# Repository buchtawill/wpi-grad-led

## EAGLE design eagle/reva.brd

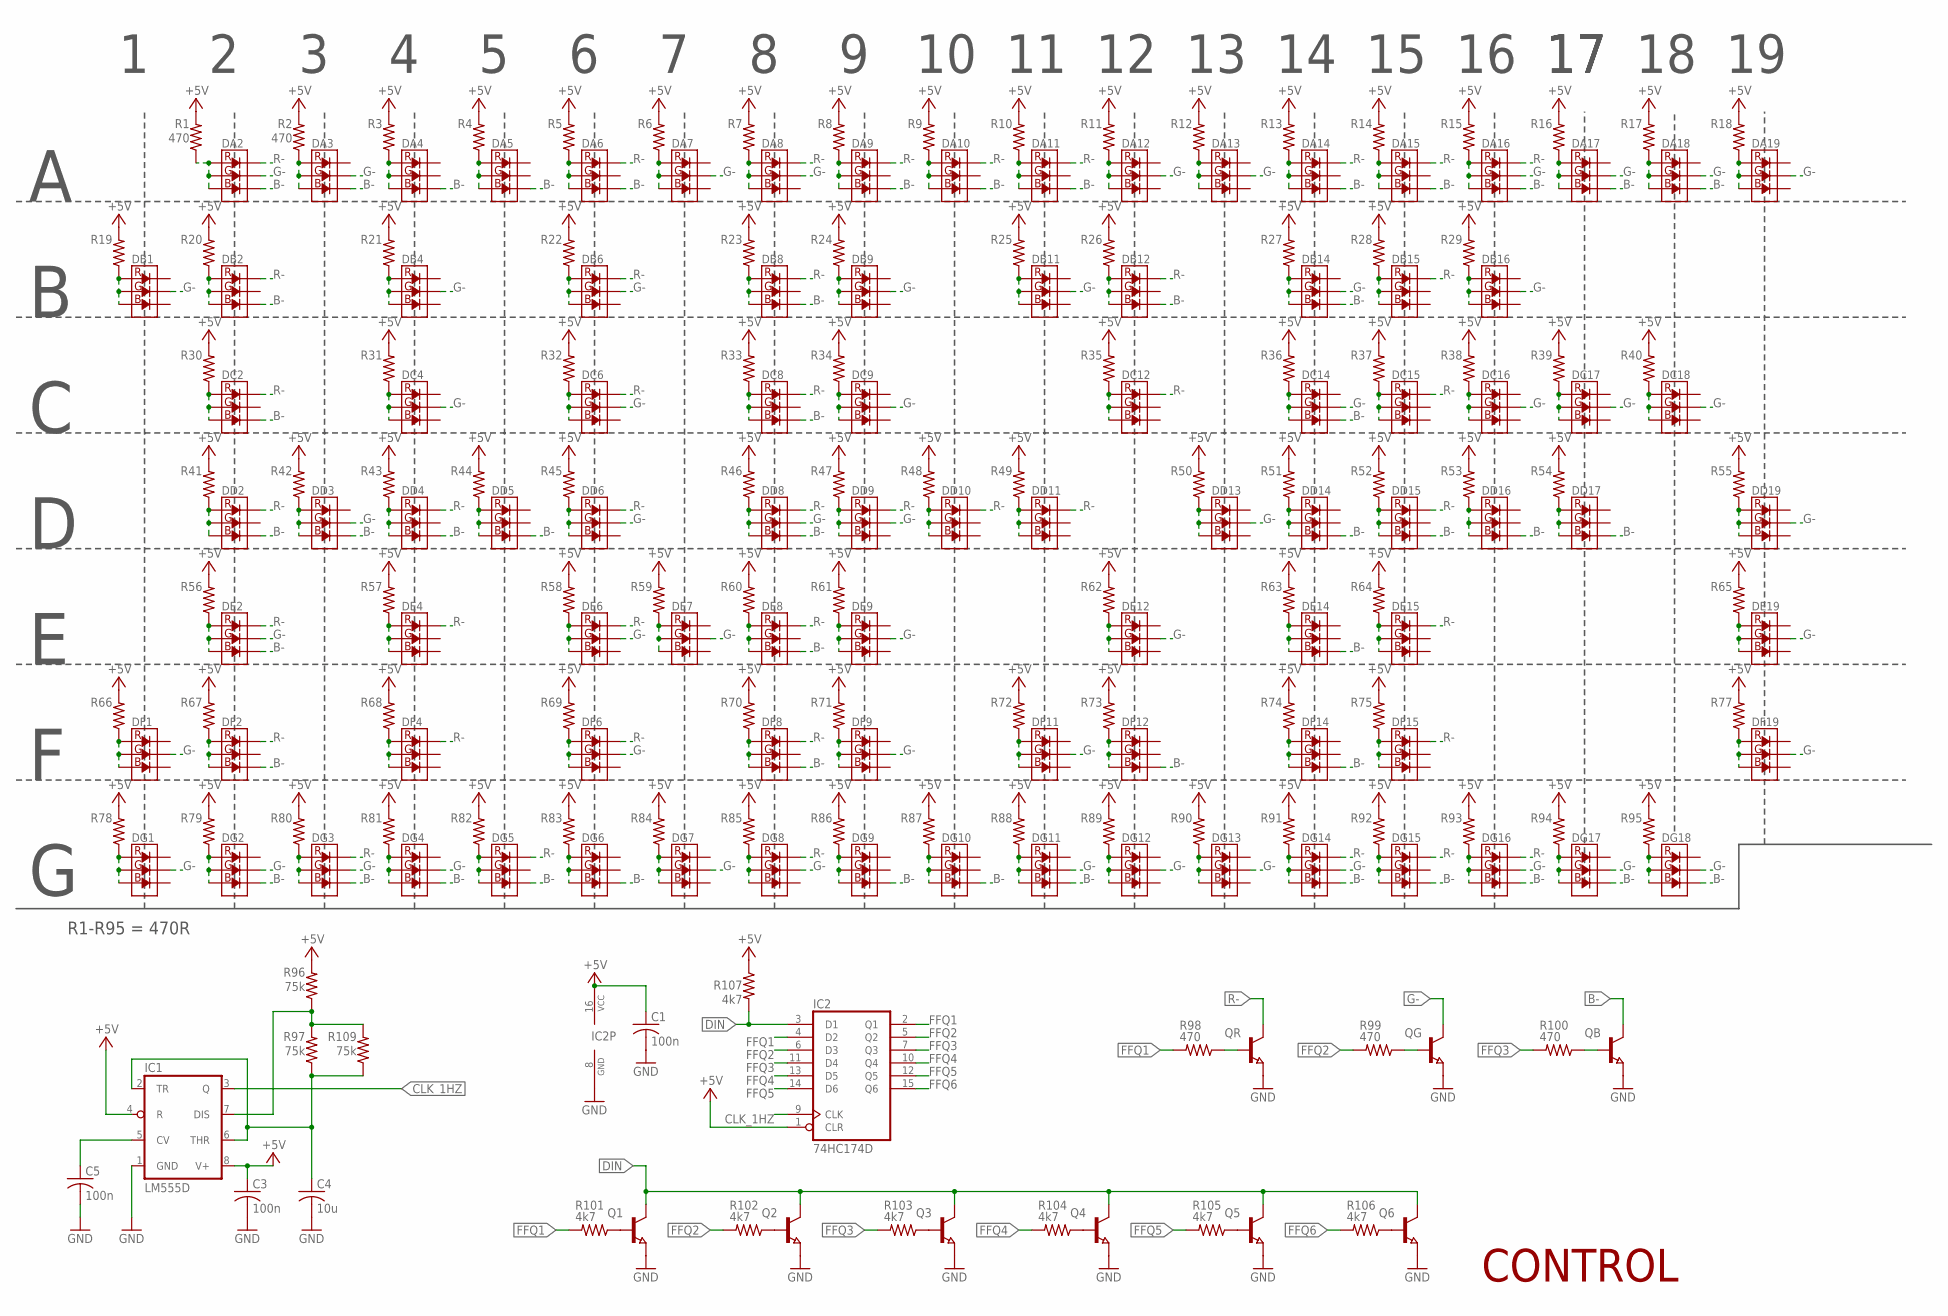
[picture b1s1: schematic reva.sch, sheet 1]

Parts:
C1, C3, C5: 100n; C0603
C4: 10u; C0805
DA2, DA3, DA4, DA5, DA6, DA7, DA8, DA9, DA10, DA11, DA12, DA13, DA14, DA15, DA16, DA17, DA18, DA19: RGB_LED_XL; LED2727
DB1, DB2, DB4, DB6, DB8, DB9, DB11, DB12, DB14, DB15, DB16: RGB_LED_XL; LED2727
DC2, DC4, DC6, DC8, DC9, DC12, DC14, DC15, DC16, DC17, DC18: RGB_LED_XL; LED2727
DD2, DD3, DD4, DD5, DD6, DD8, DD9, DD10, DD11, DD13, DD14, DD15, DD16, DD17, DD19: RGB_LED_XL; LED2727
DE2, DE4, DE6, DE7, DE8, DE9, DE12, DE14, DE15, DE19: RGB_LED_XL; LED2727
DF1, DF2, DF4, DF6, DF8, DF9, DF11, DF12, DF14, DF15, DF19: RGB_LED_XL; LED2727
DG1, DG2, DG3, DG4, DG5, DG6, DG7, DG8, DG9, DG10, DG11, DG12, DG13, DG14, DG15, DG16, DG17, DG18: RGB_LED_XL; LED2727
IC1: LM555D; SO08
IC2: 74HC174D; SO16
Q1, Q2, Q3, Q4, Q5, Q6: NPN-TRANSISTOR_SOT23; SOT23
QB: NPN-TRANSISTOR_SOT23; SOT23
QG: NPN-TRANSISTOR_SOT23; SOT23
QR: NPN-TRANSISTOR_SOT23; SOT23
R1, R2, R98, R99, R100: 470; R0603
R3, R4, R5, R6, R7, R8, R9, R10, R11, R12, R13, R14, R15, R16, R17, R18, R19, R20, R21, R22, R23, R24, R25, R26, R27, R28, R29, R30, R31, R32, R33, R34, R35, R36, R37, R38, R39, R40, R41, R42, R43, R44, R45, R46, R47, R48, R49, R50, R51, R52, R53, R54, R55, R56, R57, R58, R59, R60, R61, R62, R63, R64, R65, R66, R67, R68, R69, R70, R71, R72, R73, R74, R75, R77, R78, R79, R80, R81, R82, R83, R84, R85, R86, R87, R88, R89, R90, R91, R92, R93, R94, R95: R-US_R0603; R0603
R96, R97, R109: 75k; R0603
R101, R102, R103, R104, R105, R106, R107: 4k7; R0603

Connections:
+5V: C1.1, C3.1, IC1.4 (R), IC1.8 (V+), IC2.1 (CLR), IC2.16 (VCC), R1.2, R2.2, R3.2, R4.2, R5.2, R6.2, R7.2, R8.2, R9.2, R10.2, R11.2, R12.2, R13.2, R14.2, R15.2, R16.2, R17.2, R18.2, R19.2, R20.2, R21.2, R22.2, R23.2, R24.2, R25.2, R26.2, R27.2, R28.2, R29.2, R30.2, R31.2, R32.2, R33.2, R34.2, R35.2, R36.2, R37.2, R38.2, R39.2, R40.2, R41.2, R42.2, R43.2, R44.2, R45.2, R46.2, R47.2, R48.2, R49.2, R50.2, R51.2, R52.2, R53.2, R54.2, R55.2, R56.2, R57.2, R58.2, R59.2, R60.2, R61.2, R62.2, R63.2, R64.2, R65.2, R66.2, R67.2, R68.2, R69.2, R70.2, R71.2, R72.2, R73.2, R74.2, R75.2, R77.2, R78.2, R79.2, R80.2, R81.2, R82.2, R83.2, R84.2, R85.2, R86.2, R87.2, R88.2, R89.2, R90.2, R91.2, R92.2, R93.2, R94.2, R95.2, R96.2, R107.1; also elsewhere on the board
B-: DA2.1 (B-), DA3.1 (B-), DA4.1 (B-), DA5.1 (B-), DA6.1 (B-), DA9.1 (B-), DA10.1 (B-), DA11.1 (B-), DA14.1 (B-), DA15.1 (B-), DA16.1 (B-), DA17.1 (B-), DA18.1 (B-), DB2.1 (B-), DB8.1 (B-), DB12.1 (B-), DB14.1 (B-), DC2.1 (B-), DC8.1 (B-), DC14.1 (B-), DD2.1 (B-), DD3.1 (B-), DD4.1 (B-), DD5.1 (B-), DD8.1 (B-), DD14.1 (B-), DD15.1 (B-), DD16.1 (B-), DD17.1 (B-), DE2.1 (B-), DE8.1 (B-), DE14.1 (B-), DF2.1 (B-), DF8.1 (B-), DF12.1 (B-), DF14.1 (B-), DG2.1 (B-), DG3.1 (B-), DG4.1 (B-), DG5.1 (B-), DG6.1 (B-), DG9.1 (B-), DG10.1 (B-), DG11.1 (B-), DG14.1 (B-), DG15.1 (B-), DG16.1 (B-), DG17.1 (B-), DG18.1 (B-), QB.3 (C)
CLK_1HZ: IC1.3 (Q), IC2.9 (CLK)
CV: C5.1, IC1.5 (CV)
DIN: IC2.3 (D1), Q1.3 (C), Q2.3 (C), Q3.3 (C), Q4.3 (C), Q5.3 (C), Q6.3 (C), R107.2
DIS: IC1.7 (DIS), R96.1, R97.2, R109.2
FFQ1: IC2.2 (Q1), IC2.4 (D2), R98.2, R101.2
FFQ2: IC2.5 (Q2), IC2.6 (D3), R99.2, R102.2
FFQ3: IC2.7 (Q3), IC2.11 (D4), R100.2, R103.2
FFQ4: IC2.10 (Q4), IC2.13 (D5), R104.2
FFQ5: IC2.12 (Q5), IC2.14 (D6), R105.2
FFQ6: IC2.15 (Q6), R106.2
G-: DA2.2 (G-), DA3.2 (G-), DA7.2 (G-), DA8.2 (G-), DA12.2 (G-), DA13.2 (G-), DA16.2 (G-), DA17.2 (G-), DA18.2 (G-), DA19.2 (G-), DB1.2 (G-), DB4.2 (G-), DB6.2 (G-), DB9.2 (G-), DB11.2 (G-), DB14.2 (G-), DB16.2 (G-), DC4.2 (G-), DC6.2 (G-), DC9.2 (G-), DC14.2 (G-), DC16.2 (G-), DC17.2 (G-), DC18.2 (G-), DD3.2 (G-), DD6.2 (G-), DD8.2 (G-), DD9.2 (G-), DD13.2 (G-), DD19.2 (G-), DE2.2 (G-), DE6.2 (G-), DE7.2 (G-), DE9.2 (G-), DE12.2 (G-), DE19.2 (G-), DF1.2 (G-), DF6.2 (G-), DF9.2 (G-), DF11.2 (G-), DF19.2 (G-), DG1.2 (G-), DG2.2 (G-), DG3.2 (G-), DG4.2 (G-), DG7.2 (G-), DG8.2 (G-), DG11.2 (G-), DG12.2 (G-), DG13.2 (G-), DG14.2 (G-), DG16.2 (G-), DG17.2 (G-), DG18.2 (G-), QG.3 (C)
GND: C1.2, C3.2, C4.2, C5.2, IC1.1 (GND), IC2.8 (GND), Q1.2 (E), Q2.2 (E), Q3.2 (E), Q4.2 (E), Q5.2 (E), Q6.2 (E), QB.2 (E), QG.2 (E), QR.2 (E); also elsewhere on the board
unnamed: DA2.4 (R+), DA2.5 (G+), DA2.6 (B+), R1.1
unnamed: DA3.4 (R+), DA3.5 (G+), DA3.6 (B+), R2.1
unnamed: DA4.4 (R+), DA4.5 (G+), DA4.6 (B+), R3.1
unnamed: DA5.4 (R+), DA5.5 (G+), DA5.6 (B+), R4.1
unnamed: DA6.4 (R+), DA6.5 (G+), DA6.6 (B+), R5.1
unnamed: DA7.4 (R+), DA7.5 (G+), DA7.6 (B+), R6.1
unnamed: DA8.4 (R+), DA8.5 (G+), DA8.6 (B+), R7.1
unnamed: DA9.4 (R+), DA9.5 (G+), DA9.6 (B+), R8.1
unnamed: DA10.4 (R+), DA10.5 (G+), DA10.6 (B+), R9.1
unnamed: DA11.4 (R+), DA11.5 (G+), DA11.6 (B+), R10.1
unnamed: DA12.4 (R+), DA12.5 (G+), DA12.6 (B+), R11.1
unnamed: DA13.4 (R+), DA13.5 (G+), DA13.6 (B+), R12.1
unnamed: DA14.4 (R+), DA14.5 (G+), DA14.6 (B+), R13.1
unnamed: DA15.4 (R+), DA15.5 (G+), DA15.6 (B+), R14.1
unnamed: DA16.4 (R+), DA16.5 (G+), DA16.6 (B+), R15.1
unnamed: DA17.4 (R+), DA17.5 (G+), DA17.6 (B+), R16.1
unnamed: DA18.4 (R+), DA18.5 (G+), DA18.6 (B+), R17.1
unnamed: DA19.4 (R+), DA19.5 (G+), DA19.6 (B+), R18.1
unnamed: DB1.4 (R+), DB1.5 (G+), DB1.6 (B+), R19.1
unnamed: DB2.4 (R+), DB2.5 (G+), DB2.6 (B+), R20.1
unnamed: DB4.4 (R+), DB4.5 (G+), DB4.6 (B+), R21.1
unnamed: DB6.4 (R+), DB6.5 (G+), DB6.6 (B+), R22.1
unnamed: DB8.4 (R+), DB8.5 (G+), DB8.6 (B+), R23.1
unnamed: DB9.4 (R+), DB9.5 (G+), DB9.6 (B+), R24.1
unnamed: DB11.4 (R+), DB11.5 (G+), DB11.6 (B+), R25.1
unnamed: DB12.4 (R+), DB12.5 (G+), DB12.6 (B+), R26.1
unnamed: DB14.4 (R+), DB14.5 (G+), DB14.6 (B+), R27.1
unnamed: DB15.4 (R+), DB15.5 (G+), DB15.6 (B+), R28.1
unnamed: DB16.4 (R+), DB16.5 (G+), DB16.6 (B+), R29.1
unnamed: DC2.4 (R+), DC2.5 (G+), DC2.6 (B+), R30.1
unnamed: DC4.4 (R+), DC4.5 (G+), DC4.6 (B+), R31.1
unnamed: DC6.4 (R+), DC6.5 (G+), DC6.6 (B+), R32.1
unnamed: DC8.4 (R+), DC8.5 (G+), DC8.6 (B+), R33.1
unnamed: DC9.4 (R+), DC9.5 (G+), DC9.6 (B+), R34.1
unnamed: DC12.4 (R+), DC12.5 (G+), DC12.6 (B+), R35.1
unnamed: DC14.4 (R+), DC14.5 (G+), DC14.6 (B+), R36.1
unnamed: DC15.4 (R+), DC15.5 (G+), DC15.6 (B+), R37.1
unnamed: DC16.4 (R+), DC16.5 (G+), DC16.6 (B+), R38.1
unnamed: DC17.4 (R+), DC17.5 (G+), DC17.6 (B+), R39.1
unnamed: DC18.4 (R+), DC18.5 (G+), DC18.6 (B+), R40.1
unnamed: DD2.4 (R+), DD2.5 (G+), DD2.6 (B+), R41.1
unnamed: DD3.4 (R+), DD3.5 (G+), DD3.6 (B+), R42.1
unnamed: DD4.4 (R+), DD4.5 (G+), DD4.6 (B+), R43.1
unnamed: DD5.4 (R+), DD5.5 (G+), DD5.6 (B+), R44.1
unnamed: DD6.4 (R+), DD6.5 (G+), DD6.6 (B+), R45.1
unnamed: DD8.4 (R+), DD8.5 (G+), DD8.6 (B+), R46.1
unnamed: DD9.4 (R+), DD9.5 (G+), DD9.6 (B+), R47.1
unnamed: DD10.4 (R+), DD10.5 (G+), DD10.6 (B+), R48.1
unnamed: DD11.4 (R+), DD11.5 (G+), DD11.6 (B+), R49.1
unnamed: DD13.4 (R+), DD13.5 (G+), DD13.6 (B+), R50.1
unnamed: DD14.4 (R+), DD14.5 (G+), DD14.6 (B+), R51.1
unnamed: DD15.4 (R+), DD15.5 (G+), DD15.6 (B+), R52.1
unnamed: DD16.4 (R+), DD16.5 (G+), DD16.6 (B+), R53.1
unnamed: DD17.4 (R+), DD17.5 (G+), DD17.6 (B+), R54.1
unnamed: DD19.4 (R+), DD19.5 (G+), DD19.6 (B+), R55.1
unnamed: DE2.4 (R+), DE2.5 (G+), DE2.6 (B+), R56.1
unnamed: DE4.4 (R+), DE4.5 (G+), DE4.6 (B+), R57.1
unnamed: DE6.4 (R+), DE6.5 (G+), DE6.6 (B+), R58.1
unnamed: DE7.4 (R+), DE7.5 (G+), DE7.6 (B+), R59.1
unnamed: DE8.4 (R+), DE8.5 (G+), DE8.6 (B+), R60.1
unnamed: DE9.4 (R+), DE9.5 (G+), DE9.6 (B+), R61.1
unnamed: DE12.4 (R+), DE12.5 (G+), DE12.6 (B+), R62.1
unnamed: DE14.4 (R+), DE14.5 (G+), DE14.6 (B+), R63.1
unnamed: DE15.4 (R+), DE15.5 (G+), DE15.6 (B+), R64.1
unnamed: DE19.4 (R+), DE19.5 (G+), DE19.6 (B+), R65.1
unnamed: DF1.4 (R+), DF1.5 (G+), DF1.6 (B+), R66.1
unnamed: DF2.4 (R+), DF2.5 (G+), DF2.6 (B+), R67.1
unnamed: DF4.4 (R+), DF4.5 (G+), DF4.6 (B+), R68.1
unnamed: DF6.4 (R+), DF6.5 (G+), DF6.6 (B+), R69.1
unnamed: DF8.4 (R+), DF8.5 (G+), DF8.6 (B+), R70.1
unnamed: DF9.4 (R+), DF9.5 (G+), DF9.6 (B+), R71.1
unnamed: DF11.4 (R+), DF11.5 (G+), DF11.6 (B+), R72.1
unnamed: DF12.4 (R+), DF12.5 (G+), DF12.6 (B+), R73.1
unnamed: DF14.4 (R+), DF14.5 (G+), DF14.6 (B+), R74.1
unnamed: DF15.4 (R+), DF15.5 (G+), DF15.6 (B+), R75.1
unnamed: DF19.4 (R+), DF19.5 (G+), DF19.6 (B+), R77.1
unnamed: DG1.4 (R+), DG1.5 (G+), DG1.6 (B+), R78.1
unnamed: DG2.4 (R+), DG2.5 (G+), DG2.6 (B+), R79.1
unnamed: DG3.4 (R+), DG3.5 (G+), DG3.6 (B+), R80.1
unnamed: DG4.4 (R+), DG4.5 (G+), DG4.6 (B+), R81.1
unnamed: DG5.4 (R+), DG5.5 (G+), DG5.6 (B+), R82.1
unnamed: DG6.4 (R+), DG6.5 (G+), DG6.6 (B+), R83.1
unnamed: DG7.4 (R+), DG7.5 (G+), DG7.6 (B+), R84.1
unnamed: DG8.4 (R+), DG8.5 (G+), DG8.6 (B+), R85.1
unnamed: DG9.4 (R+), DG9.5 (G+), DG9.6 (B+), R86.1
unnamed: DG10.4 (R+), DG10.5 (G+), DG10.6 (B+), R87.1
unnamed: DG11.4 (R+), DG11.5 (G+), DG11.6 (B+), R88.1
unnamed: DG12.4 (R+), DG12.5 (G+), DG12.6 (B+), R89.1
unnamed: DG13.4 (R+), DG13.5 (G+), DG13.6 (B+), R90.1
unnamed: DG14.4 (R+), DG14.5 (G+), DG14.6 (B+), R91.1
unnamed: DG15.4 (R+), DG15.5 (G+), DG15.6 (B+), R92.1
unnamed: DG16.4 (R+), DG16.5 (G+), DG16.6 (B+), R93.1
unnamed: DG17.4 (R+), DG17.5 (G+), DG17.6 (B+), R94.1
unnamed: DG18.4 (R+), DG18.5 (G+), DG18.6 (B+), R95.1
Q1B: Q1.1 (B), R101.1
Q2B: Q2.1 (B), R102.1
Q3B: Q3.1 (B), R103.1
Q4B: Q4.1 (B), R104.1
Q5B: Q5.1 (B), R105.1
Q6B: Q6.1 (B), R106.1
QBB: QB.1 (B), R100.1
QGB: QG.1 (B), R99.1
QRB: QR.1 (B), R98.1
R-: DA2.3 (R-), DA6.3 (R-), DA8.3 (R-), DA9.3 (R-), DA10.3 (R-), DA11.3 (R-), DA14.3 (R-), DA15.3 (R-), DA16.3 (R-), DB2.3 (R-), DB6.3 (R-), DB8.3 (R-), DB12.3 (R-), DB15.3 (R-), DC2.3 (R-), DC6.3 (R-), DC8.3 (R-), DC12.3 (R-), DC15.3 (R-), DD2.3 (R-), DD4.3 (R-), DD6.3 (R-), DD8.3 (R-), DD9.3 (R-), DD10.3 (R-), DD11.3 (R-), DD15.3 (R-), DE2.3 (R-), DE4.3 (R-), DE6.3 (R-), DE8.3 (R-), DE15.3 (R-), DF2.3 (R-), DF4.3 (R-), DF6.3 (R-), DF8.3 (R-), DF15.3 (R-), DG3.3 (R-), DG5.3 (R-), DG8.3 (R-), DG14.3 (R-), DG15.3 (R-), DG16.3 (R-), QR.3 (C)
TR: C4.1, IC1.2 (TR), IC1.6 (THR), R97.1, R109.1

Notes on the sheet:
R1-R95 = 470R
CONTROL

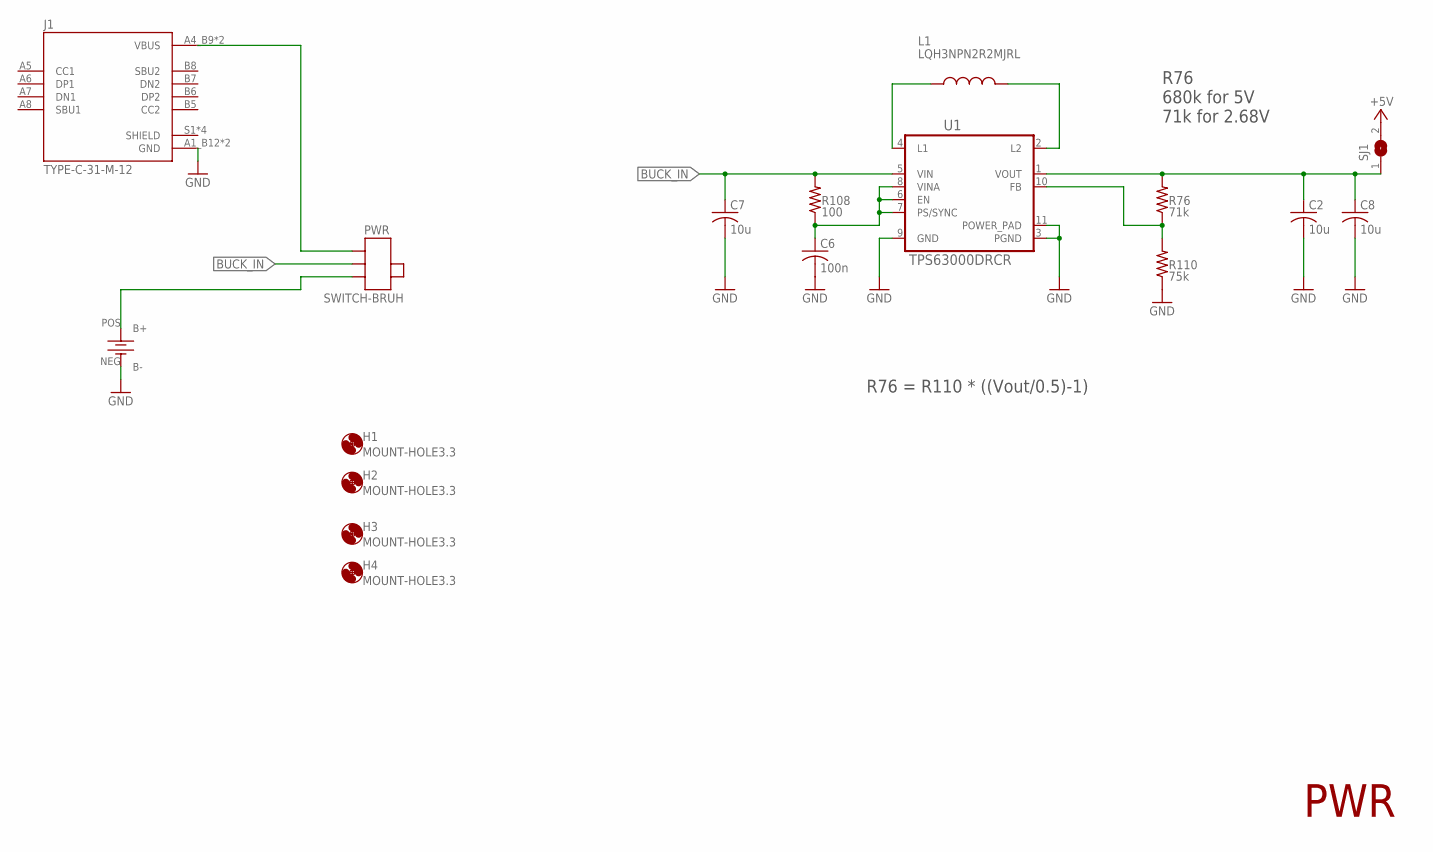
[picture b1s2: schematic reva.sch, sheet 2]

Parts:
BAT1: CR2450; CR240_CASE
C2, C7, C8: 10u; C0805
C6: 100n; C0603
H1, H2, H3, H4: MOUNT-HOLE3.3; 3,3
J1: TYPE-C-31-M-12; HRO_TYPE-C-31-M-12
L1: LQH3NPN2R2MJRL; IND_LQH3NPN2R2MJRL
PWR: SWITCH-BRUH; SW-K31391B
R76: 71k; R0603
R108: 100; R0603
R110: 75k; R0603
SJ1: SJ
U1: TPS63000DRCR; VREG_V62/16624-01YE

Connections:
5VBUCK: C2.1, C8.1, R76.2, SJ1.1, U1.1 (VOUT)
+5V: SJ1.2; also elsewhere on the board
BUCK_IN: C7.1, PWR.COM (C), R108.2, U1.5 (VIN)
GND: BAT1.NEG (B-), C2.2, C6.2, C7.2, C8.2, J1.A1_B12 (GND), J1.B1_A12 (GND), R110.1, U1.3 (PGND), U1.9 (GND), U1.11 (POWER_PAD); also elsewhere on the board
L1: L1.1, U1.4 (L1)
L2: L1.2, U1.2 (L2)
unnamed: R76.1, R110.2, U1.10 (FB)
unnamed: J1.A4_B9 (VBUS), J1.B4_A9 (VBUS), PWR.L (T1)
unnamed: BAT1.POS (B+), PWR.R (T2)
VINA: C6.1, R108.1, U1.6 (EN), U1.7 (PS/SYNC), U1.8 (VINA)

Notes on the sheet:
PWR
R76 = R110 * ((Vout/0.5)-1)
R76 680k for 5V 71k for 2.68V

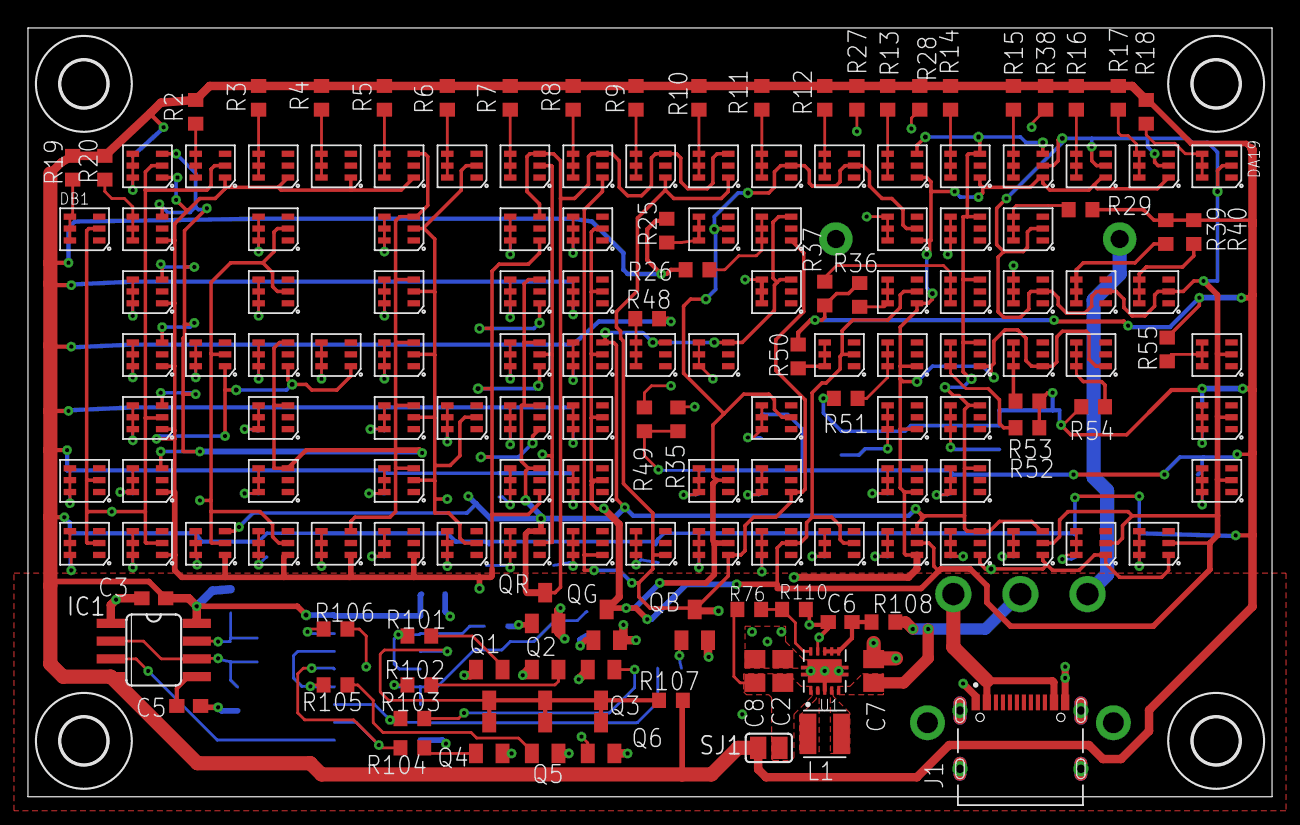
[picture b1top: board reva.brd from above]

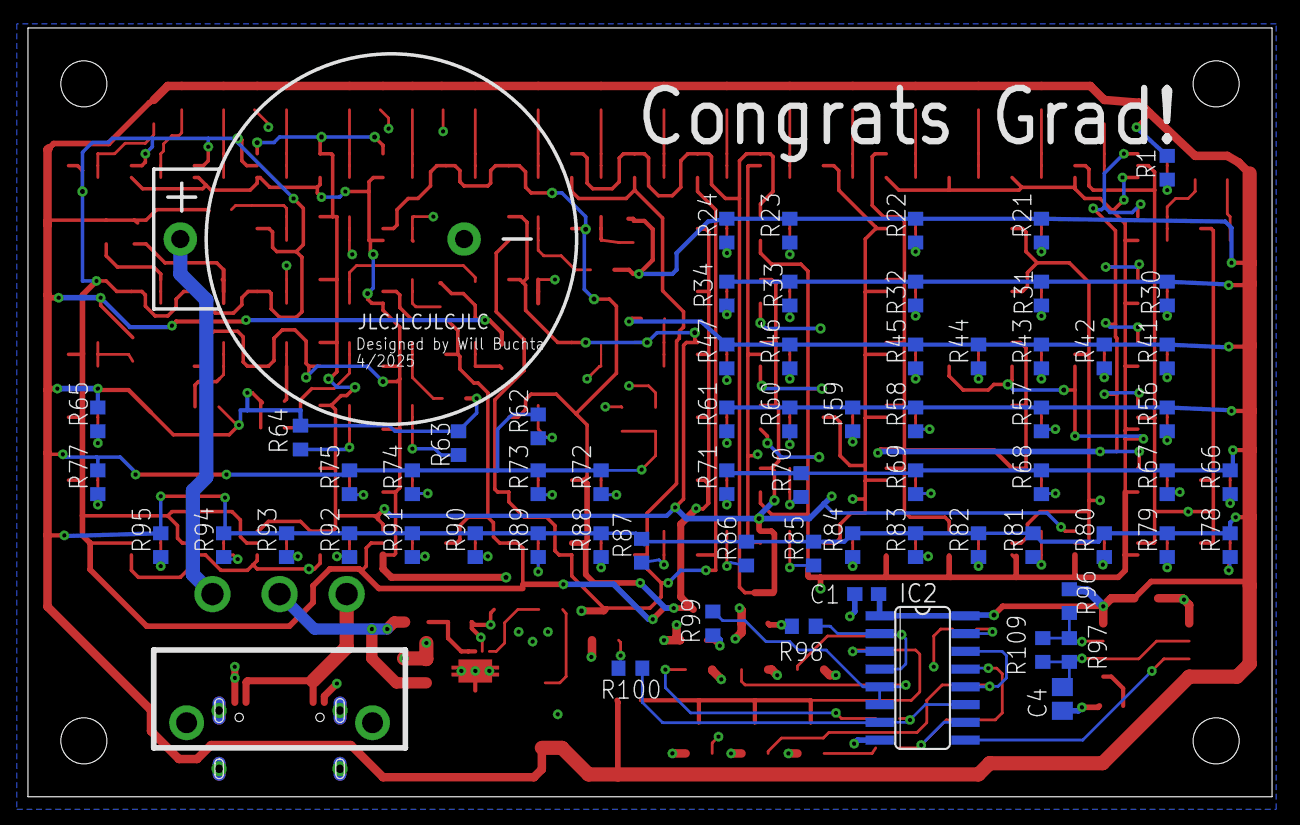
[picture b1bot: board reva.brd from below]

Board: 4 copper layers, 89.0 x 55.0 mm, 233 parts (67 on the bottom side), 127 nets.

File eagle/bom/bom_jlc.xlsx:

Qty | Value | Device | Package | Parts | JLCPCB Part Number
9 |  | NPN-TRANSISTOR_SOT23 | SOT23 | Q1, Q2, Q3, Q4, Q5, Q6, QB, QG, QR | C2150
92 | 470 | R-US_R0603 | R0603 | R3, R4, R5, R6, R7, R8, R9, R10, R11, R12, R13, R14, R15, R16, R17, R18, R19, R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 | C23179
1 | 100 | R-US_R0603 | R0603 | R108 | C23162
4 | 100n | C-USC0603 | C0603 | C1, C3, C5, C6 | C1591
5 | 10u | C-USC0805 | C0805 | C2, C4, C7, C8 | C1713
7 | 4k7 | R-US_R0603 | R0603 | R101, R102, R103, R104, R105, R106, R107 | C23162
1 | 74HC174D | 74HC174D | SO16 | IC2 | C6828
1 | 680k | R-US_R0603 | R0603 | R76 | C25822
4 | 75k | R-US_R0603 | R0603 | R96, R97, R109, R110 | C23242
1 | CR2450 | CR2450 | CR240_CASE | BAT1 | C964806
1 | LM555D | LM555D | SO08 | IC1 | C7593
1 | LQH3NPN2R2MJRL | LQH3NPN2R2MJRL | IND_LQH3NPN2R2MJRL | L1 | C9890
94 | RGB_LED_XL | RGB_LED_XL | LED2727 | DA2, DA3, DA4, DA5, DA6, DA7, DA8, DA9, DA10, DA11, DA12, DA13, DA14, DA15, DA1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 | C22461786
1 | SWITCH-BRUH | SWITCH-BRUH | SW-K31391B | PWR | C92656
1 | TPS63000DRCR | TPS63000DRCR | VREG_V62/16624-01YE | U1 | C2876573
1 | TYPE-C-31-M-12 | TYPE-C-31-M-12 | HRO_TYPE-C-31-M-12 | J1 | C165948

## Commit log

2025-04-04 Initial commit:
2025-04-04 Save board state
2025-04-05 Finish rough layout
2025-04-06 Make first prototype board
2025-04-06 Change battery holder, create BOM and PNP
2025-04-07 Fix 555 error
2025-04-08 Change buck to have 20uF Cout, increase inductor footprint size
2025-04-08 Add resistive feedback to TP63000
2025-04-13 Pre 0603 change
2025-04-14 Change pads to 0603 and move some resistors around. This commit marks final draft
2025-04-29 Add errata and future recommendations
2026-03-22 original
2026-03-22 Save
2026-03-22 Move to 2025 / 2026 folders
2026-03-22 Remove unused file
